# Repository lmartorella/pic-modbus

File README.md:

Moved to https://codeberg.org/lmartorella/esp-modbus-bridge

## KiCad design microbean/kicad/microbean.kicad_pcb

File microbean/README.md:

# Micro-bean prototype

The prototyped hardware is a small board (just 30x28mm) built around a cost-effective [Microchip PIC16F1827 MCU](https://www.microchip.com/wwwproducts/en/PIC16F1827), a RS-485 level adapter and a voltage regulator. The board expose almost all MCU lines to the maker, allowing a great amount of free digital and analog I/O pins.

## Schematic

The schematics is oriented to simplicity and stability.

The board accepts unregulated power, to allow to use 4-wire cable for data and power.

The voltage regulation is delegated to a classic `78xx` series regulator, to be compatible with a wide range of line input voltage. A series diode saves the boards from inverted wiring. The electrolytic capacitors are oversized to comply with electric surges.

Since the regulated voltage is exposed through the headers to power any attached hardware (sensors, small displays, etc...), the regulator should be dimensioned to provide the required current (depending also from the voltage swing of the power line).

Each boards can be fitted with either 5V or 3.3V regulator, without any issue for the MCU that supports a wide input voltage. This enables a range of sensors to be directly connected to the MCU ports without requiring any level adapter.

A full-sized In-Circuit Serial Programmer for the MCU port is provided, with classic 0.1" pitch, to provide direct programming feature.

The RS485 bus adapter IC should be fitted based on the voltage regulator. Both voltage flavours are available from ST (`ST485`/`ST3485`).

The rest of the small board is occupied a micro-switch (that can be used as a reset or zero-configuration switch), the status LED, external connectors and the 4-wire screw-type terminals (power and RS485 bus).

## The Microcontroller

The selected MCU is the [PIC16L1827](https://www.microchip.com/wwwproducts/en/PIC16F1827) from Microchip, a mid-range 8-bit CPU with 4K-word program memory that gives a great selection of features in a small SO18 package that can be still soldered without requiring specialized tools.

In addition, pins can be configured with some degree of freedom in order to expose the hardware features as required.   

The following MCU lines are used to connect the bean to the RS485 bus, hence are not usually available for design:

- `RB2` as `UART RX`
- `RB5` as `UART TX`
- `RA6` for `RS485` line arbitration
- `RA5/MCLR` for reset/zero-configuration button
- `RA7` for status led

In addition these lines are shared with `ICSP` header:
- `RB6` with `ICSP CLK`
- `RB7` with `ICSP DAT`

The configuration then leaves a total of 11 GPIO pins to the designer.

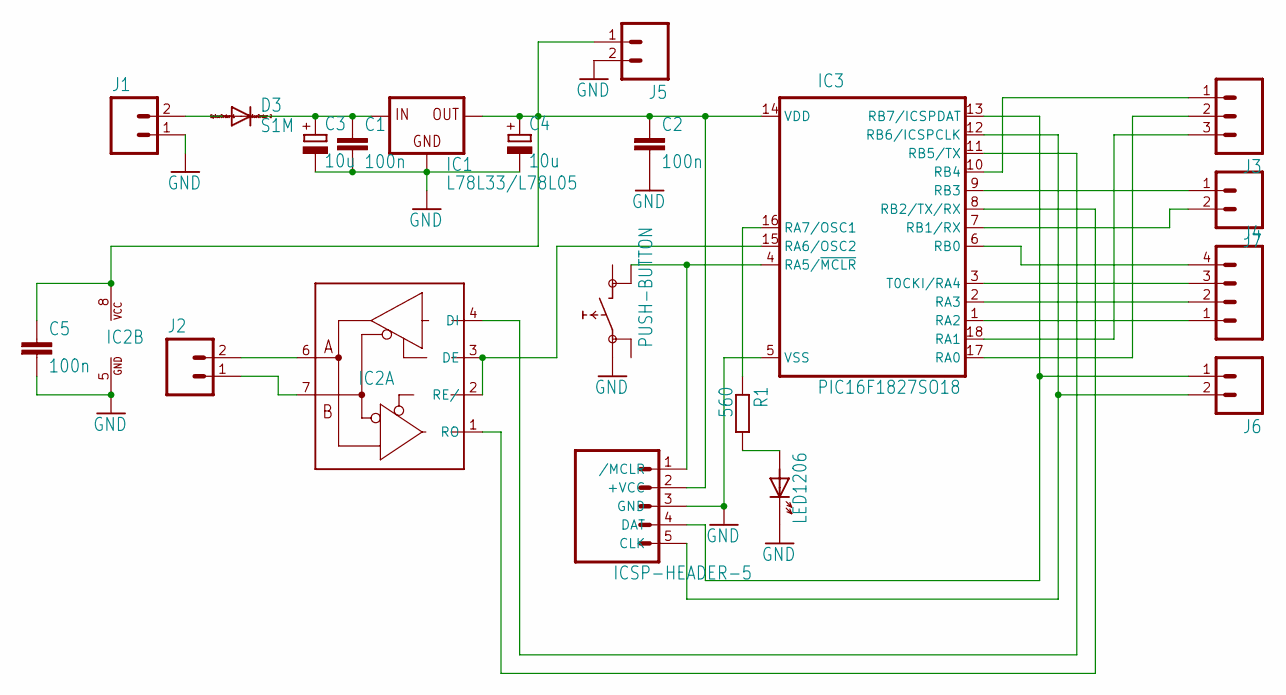
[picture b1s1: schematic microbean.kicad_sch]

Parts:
C1, C2, C5: 100n; C0805
C3, C4: 10u; UD-4X5,8_NICHICON
D2: LED1206; CHIPLED_1206
D3: S1M; SMA
IC1: L78L33/L78L05; SOT89
IC2: MAX485ST3485; SO08
IC3: PIC16F1827SO18; SO18W
ICSP0: ICSP-HEADER-5; 1X05
J1, J2: M02-SCREW-3.5MM3.5MM; SCREWTERMINAL-3.5MM-2
J3: M03; 1X03
J4: M04; 1X04
J5, J6, J7: M02; 1X02
R1: 560; R0805
U$2: PUSH-BUTTON; MICRO-SWITCH

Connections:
A: IC2.6 (A), J2.2
B: IC2.7 (B), J2.1
GND: C1.2, C2.2, C3.-, C4.-, C5.2, D2.C (K), IC1.2 (GND), IC1.2@1 (GND), IC2.5 (GND), IC3.5 (VSS), ICSP0.3 (GND), J1.1, J5.2, U$2.1 (0@A)
MCLR: IC3.4 (RA5/~MCLR), ICSP0.1 (/MCLR), U$2.4 (1@B)
unnamed: D3.A, J1.2
unnamed: C1.1, C3.+, D3.C, IC1.3 (IN)
unnamed: D2.A, R1.2
RA0: IC3.17 (RA0), J3.2
RA1: IC3.18 (RA1), J3.3
RA2: IC3.1 (RA2), J4.1
RA3: IC3.2 (RA3), J4.2
RA4: IC3.3 (T0CKI/RA4), J4.3
RA6: IC2.2 (RE/), IC2.3 (DE), IC3.15 (RA6/OSC2)
RA7: IC3.16 (RA7/OSC1), R1.1
RB0: IC3.6 (RB0), J4.4
RB1: IC3.7 (RB1/RX), J7.2
RB2: IC2.1 (RO), IC3.8 (RB2/TX/RX)
RB3: IC3.9 (RB3), J7.1
RB4: IC3.10 (RB4), J3.1
RB5: IC2.4 (DI), IC3.11 (RB5/TX)
RB6: IC3.12 (RB6/ICSPCLK), ICSP0.5 (CLK), J6.2
RB7: IC3.13 (RB7/ICSPDAT), ICSP0.4 (DAT), J6.1
VCC: C2.1, C4.+, C5.1, IC1.1 (OUT), IC2.8 (VCC), IC3.14 (VDD), ICSP0.2 (+VCC), J5.1

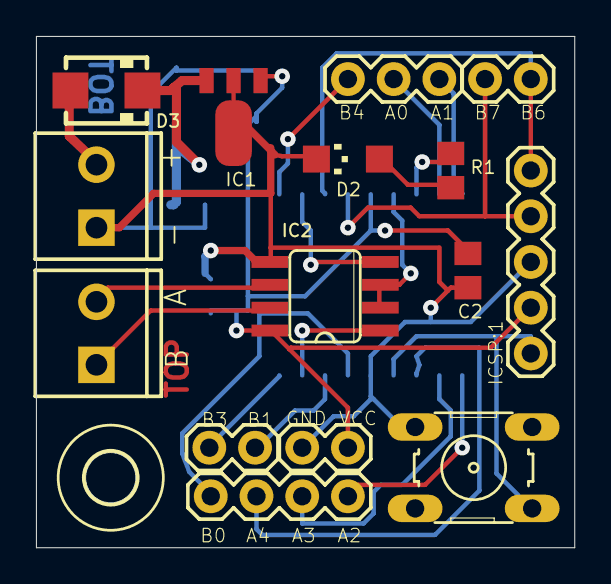
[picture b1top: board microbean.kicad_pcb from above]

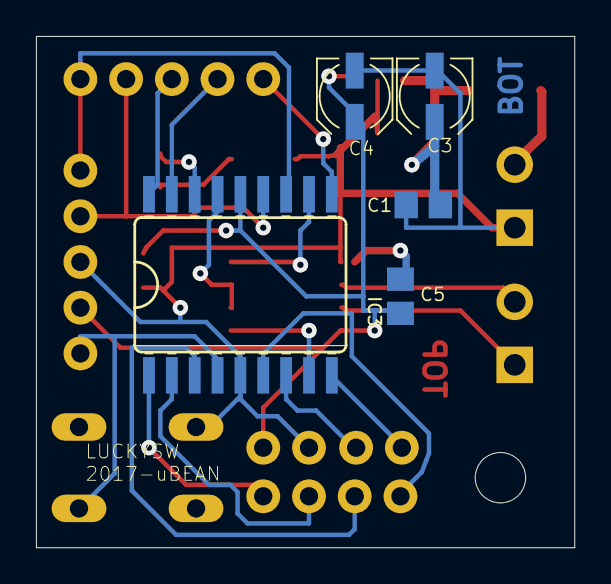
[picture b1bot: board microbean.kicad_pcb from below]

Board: 2 copper layers, 29.9 x 28.4 mm, 21 parts (5 on the bottom side), 23 nets.

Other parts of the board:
U$4: 2,8

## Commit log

2019-04-23 - Restructuring folders to split app from lib
2019-05-17 - Documenting
2019-07-03 - Added doc for ubean - Documenting
2019-07-03 - Removed test apps
2019-07-03 - Removed old tests, start folder refactoring
2019-07-03 - Folder refactoring
2019-07-03 - Refactoring firmware code
2019-07-03 Compiles the microbean
2019-07-03 - Fixed garden sample build - Removed main bean project (in samples now) - Moved netmaster in samples
2019-07-03 - Renamed sample project
2019-07-03 - Fixed NET MCU - Project cleanup
2019-07-03 - Fixed NetBeans project for Raspbian
2019-10-12 - Code fix and documentation
2019-11-03 - Renamed project for micro-bean - Fixed samples/sdk separation for sinks
2019-11-03 - Implemented digital input with last event table (for high resolution event log) - Not tested yet
2020-03-22 - Added sink documentation
2020-03-23 - Added digital input simulator and tester device
2020-03-23 - Fixed serialization of JSON - Added node removal from simulator UI - Fixed UT
2020-03-23 - Implemented flow reading from bus
2020-03-24 - Fixed raspberry netmaster build
2020-03-25 - Fixed digio hw and c# sink driver
2020-03-26 - Added debounce to digital input, at 0.1s (for normal switches and relais)
2020-03-29 - Fixed management of bean MCLR for idx update - Added persistence log for raspberry - Fixed server exception in case of stream dispose
2020-04-04 - Added statistics log in raspberry master nodes to analyze disconnection loop - Fixed TCP management in server to avoid loop of connections and disconnections, and refactor code to improve readabili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
2020-04-13 - Fixed solar TCP open/close loop - Added logs to listen socket issue on raspbian (missing POLLINVALID check?)
2020-04-19 - Added analog integrator code - Upgraded micro_bean project MPLAB version
2020-04-19 - Upgraded and fixed mcu card prod
2020-04-19 - Readded proto board settings - Fixed new project upgrade
2020-04-22 - Done
2020-05-03 - Found issue in waiting the PL011 raspberrys to be clear sometimes
2020-05-04 - Fixed memory corruption in stats_raspbian.c
2020-05-08 - Fixed raspberry loop due to stale TCP connection: now keep-alive is set - Fixed issue in unzombie
2020-05-09 - Clean up and some doc
2020-05-10 - Fixed reset reason in microBean: software exception was reported as MCrl, causing zero-configuration address assignment - Using real pointers instead of BYTE used for older PIC models
2020-05-10 - Added a way to immediately re-fetch status in case of sub-node errors
2020-05-13 - Restored bmp180 sample
2020-05-13 - Optimized check in case of node error notification - Added tester code to raise exception at timer
2020-05-13 - Upgraded HTBT message with child list - Simplified heartbeat management in case of zombie child or new child
2020-05-13 - Fixed exception text in microbean
2022-10-20 - Initial refolder - Name linting
2022-10-20 - Switched to CMake
2022-10-20 - Silenced warnings
2022-10-22 Moved main and splitted
2022-10-23 - Splitting primary/secondary bus srcs
2022-10-25 - Migrated XC8 projects to C99
2022-10-25 - Converted raspberry too to C99
2022-10-25 - Migrated garden as well
2022-10-26 - Linted
2022-10-27 - Splitting code by module instead of by pragma - Rationalized folders
2022-10-27 - Renamed inc to c
2022-10-27 - RS485 and bus by default
2022-10-29 - Better split between prim/sec and protocol
2022-10-29 - Alignment on PIC side
2022-10-29 - Finishing up
2022-10-29 linux to posix
2022-10-29 - Cleanup
2022-10-31 - Fixed poll on posix
2022-10-31 - WIP cmake lib
2022-11-01 - Sources and includes refactoring
2022-11-01 - Removing macro between sec/prim
2022-11-01 - Relocated headers
2022-11-02 - Posix target is building
2022-11-02 - Removed RS232 as debug line
2022-11-02 - Cleanup for last exception
2022-11-05 - Fixed build on eth card
2022-11-05 - Adding micro_bean as well
2022-11-05 - Enabling all the sample sinks
2022-11-06 - Removed warnings
2022-11-06 - Fixed persistence user data: 16 bytes
2022-11-06 - Fixed microbean
2022-11-06 - New main loop
2022-11-06 - Moved away DEBUG
2023-01-03 - WIP
2023-01-03 - WIP2
2023-01-04 wip2
2023-01-04 - Exploded uart PIC (required mid-range MCU with 16 stack depth) - Reintroduced modulo (it was used anyway)
2023-01-09 - TDD
2023-01-10 - Testing buffers
2023-01-10 - Add overrun checks
2023-01-10 - Test write abort
2023-01-10 - Test coalesce writes
2023-01-10 - Test hardware overrun errors
2023-01-10 - Implemented frame error API and tested
2023-01-11 - Restored old protocol files
2023-01-12 - Fixed lib build, removed RTU client
2023-01-12 - Further renaming
2023-01-14 - Priming new bus client RTU for TDD
2023-01-14 - Move address persistence outside
2023-01-16 - WIP tests
2023-01-16 - Introduced skip
2023-01-16 - Tested mark condition
2023-01-17 - Other tests
2023-01-18 - Test and fixed sizes
2023-01-18 - Done complete messages
2023-01-19 - Added CRC and TDD
2023-01-19 - CRC working
2023-01-19 - More CRC tests and fixes
2023-01-19 - Added data to messages
2023-01-21 - New API for modbus function, that requires complete buffer to be avail
2023-01-21 - Implemented function streams
2023-01-22 - Implemented
2023-01-22 - Testing multi-pass stream
2023-01-23 - MPLAB prj update
2023-01-23 - Fixed
2023-01-24 - Removed protocol and sinks file
2023-01-24 - Adding sys function table
2023-01-24 - Fixed build
2023-01-26 - Added tests for system sinks
2023-01-29 - Testing the Simulator with Stimuli
2023-01-29 - Tests
2023-01-29 - Removed old define
2023-01-29 - Test for CRC error
2023-01-29 - Imported lib as source files, otherwise debugging lib source files is impossible in MPLAB
2023-01-29 - Centralized management of RX/TX drivers - Alternate driver configuration in Simulator to allow stimuli to work
2023-01-29 - Getting mad with SCL
2023-01-30 - Reduced displacement operator that would require imul on PIC
2023-01-30 - Removed div as well
2023-01-30 - Helping hand for XC8 compiler
2023-01-30 - Small opts
2023-02-02 - Massive optimization for XC8: removed local vars, using global buffer, and adapted API
2023-02-02 - Mmm not so great actually
2023-02-02 - Using new XC8 capabilites for __eeprom
2023-02-02 - Cleanup naming
2023-02-04 - Fixed build on posix
2023-02-05 - Fixed CRC error on PIC target
2023-02-05 - Added CRC tests
2023-02-05 - Preparing env
2023-02-10 - Hacked the dongle
2023-02-19 - Added visual test for timer settings
2023-02-19 - Fixed some flags and timing after HW debug
2023-02-19 - Fixed function 3 response
2023-02-19 - Support for hard-coded bus station, for testing
2023-02-19 - Boost to 16Mhz
2023-02-19 - Fixed strange xc8 compiler issue
2023-02-19 - Fixed read flow
2023-02-19 Better timings
2023-02-19 - Add support to disable persistence
2023-02-19 - Fixed int overflow issue in C 16-bit compilers
2023-02-19 - Report CRC errors (without auto-reset)
2023-02-20 - Reducing footprint (from 39% to 36%) collapsing sys and app functions and using standard slots of 8 registers for each function
2023-02-20 - Disabled code (and constants), down to 34% now
2023-02-20 - Down to 31%, strange XC8 optimizations
2023-02-21 - Single reset reason, no more string-based exc string - Down to 29% - Code cleanup
2023-02-21 - Completed autoconf protocol
2023-02-26 - Trying to use 16-bit registers in sys nodes
2023-03-05 - Adding some auto-conf info in gateway
2023-03-05 - Migrating bmp180 code
2023-03-16 - Start of pic-modbus smaller project - Starting new code base without Posix target - Removed master bus code as well - Removed autoconf specialized protocol
2023-03-16 - Merged auto_conf_functions and sys to registers
2023-03-16 - Removed leds and persistence from core
2023-03-16 - Removed tests, platform unuseable
2023-03-16 - Externalized sys registers and whole address space validation
2023-03-16 - Refoldered samples - Removed RS232 software (ex-solar) - Removed display
2023-03-16 - File rename
2023-03-16 - Implemented led blinker sample with register mapping - Refactored pic configuration files
2023-03-16 - Removed mapping, added sys
2023-03-25 - Compile-time big-ending translation
2023-03-25 - Using multi-register approach for bmp180
2023-03-25 - Fixed i2c
2023-05-13 - Moved folder to new git structure
2023-05-14 - Folder renamed - Removed old PIC targets - Fixed UTs
2023-05-14 - Added some docs
2023-06-20 - Working with TCP transactions
2023-06-21 - Working log to telnet port
2023-07-25 - Renamed net with modbus and bus with rtu
2023-07-25 - Added radio medium configuration - Disabled CRC with radio
2023-07-26 - Fixed UTs
2023-07-26 - WIP raspberry test app
2023-07-27 - WIP dev
2023-07-27 - Proper register init using masks - Tests
2023-07-27 - FIxed static usage using include
2023-07-27 - Make rs485 state internal
2023-07-27 - WIP read mode
2023-07-27 - WIP write
2023-07-28 - Added dump of version ID
2023-07-28 - SPI done
2023-07-28 - Added gpio for reset
2023-07-28 - Setup working on raspberry 2
2023-07-28 - Fixed TX framer usage
2023-07-28 - RX state machine should be OK now
2023-07-28 - Receiving some CRC errors with 0 syncword (other devices?)
2023-07-29 - Splitted radio from lt8920 hw
2023-07-29 - Support for two modules in the same bus
2023-07-29 - No max TX power for in-house tests
2023-07-29 - Hacking the framer state
2023-07-29 - Configurable LT8920_FIRST_BYTE_AS_LENGTH - Fixed side reset bug
2023-07-29 - Hacking the framer
2023-07-29 - Found the buggy SYNCWORD 64 bit support!
2023-07-30 - WIP refactoring to accomodate radio in PIC
2023-07-30 - Make it compile on XC8
2023-11-05 - Moved to solar
2023-11-05 - Removed leftover
2023-11-12 - Documentation update - Added KiCad schematics of the microbean
2026-02-02 - Doc
2026-02-02 - Added 2 error codes
2026-02-04 - onSend called before opening the frame to allow error reporting and more timeout
